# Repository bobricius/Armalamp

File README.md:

# Armalamp
Plastic covered photo cells + Supercapacitor with unlimited life ( 1369years )

Winner: Planet Friendly Power: Hackaday Prize 2022 Round Finalist!

Features:

- 6x BPW34 photodiodes aka solar cell
(plastic diodes, more resistant to damage against glass solar cell)

- Up to 20F supercapacitor
(You can use bigger capacity but 20F is optimal for charge in one sunny day)

- 4 hours operation in night depends on intensity

- Auto night on

- Step up converter effective use all stored energy, discharge scap until 0.3V !!!!!!

- Output is activated in night

SuperCapacitor can achieve 500 000 charging cycles, it is enough for 1369years.
(BPW34 photodiode act as solar cell, MCP1624 suck all stored energy to LED because can work until 0.3V)

https://hackaday.io/project/185116-armalamp-armageddon-resistant-night-lamp

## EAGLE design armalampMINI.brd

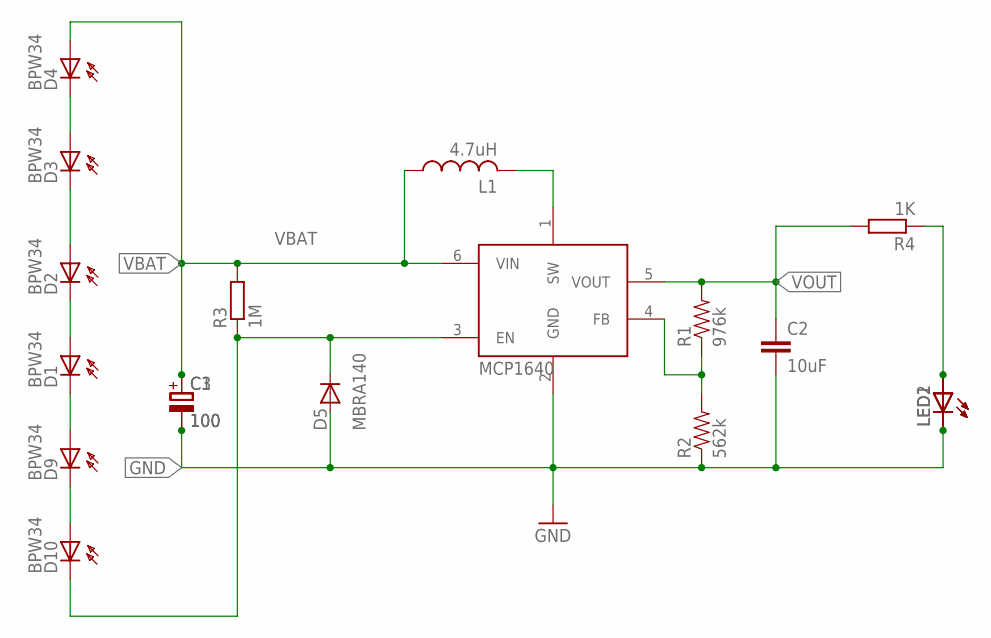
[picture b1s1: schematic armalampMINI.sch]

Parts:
C1, C3: 100; TT2D7L
C2: 10uF; 0805
D1, D2, D3, D4, D9, D10: BPW34; BP104
D5: MBRA140; SOD-323
L1: 4.7uH; LQH44
LED1: LED5MM
LED2: LEDKA-3528ASYC; KA-3528ASYC
R1: 976k; 0805
R2: 562k; 0805
R3: 1M; R0603
R4: 1K; R0603
U1: MCP1640; SOT23-6

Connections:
GND: C1.-, C2.2, C3.-, D5.2 (A), LED1.K (C), LED2.C, R2.1, U1.2 (GND)
unnamed: L1.P$2 (2), U1.1 (SW)
unnamed: R1.1, R2.2, U1.4 (FB)
unnamed: D3.A, D4.K (C)
unnamed: D5.1 (C), D10.K (C), R3.1, U1.3 (EN)
unnamed: LED1.A, LED2.A, R4.1
unnamed: D9.K (C), D10.A
unnamed: D1.K (C), D9.A
unnamed: D1.A, D2.K (C)
unnamed: D2.A, D3.K (C)
VBAT: C1.+, C3.+, D4.A, L1.P$1 (1), R3.2, U1.6 (VIN)
VOUT: C2.1, R1.2, R4.2, U1.5 (VOUT)

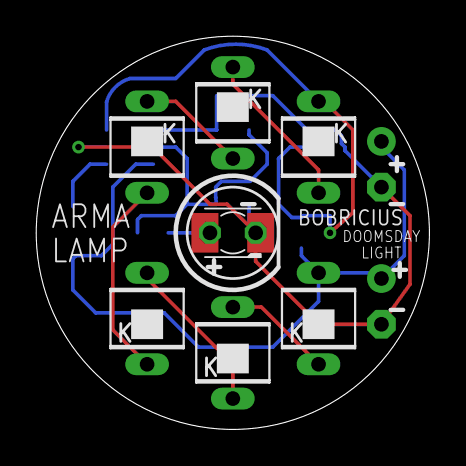
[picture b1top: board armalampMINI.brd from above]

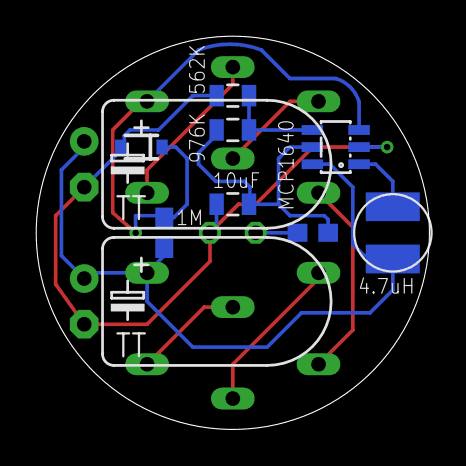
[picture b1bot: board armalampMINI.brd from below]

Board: 2 copper layers, 21.8 x 21.8 mm, 18 parts (10 on the bottom side), 12 nets.

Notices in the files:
parts and their libraries:
SparkFun: Licensing: CC v3.0 Share-Alike You are welcome to use this library for commercial purposes.
